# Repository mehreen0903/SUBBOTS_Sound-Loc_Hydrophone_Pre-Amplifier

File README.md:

# SUBBOTS_Sound-Loc_Hydrophone_Pre-Amplifier
This repo contains the PCB that acts as the pre-amplifier for the signal from the 5 hydrophones. This will later feed into the DE10.

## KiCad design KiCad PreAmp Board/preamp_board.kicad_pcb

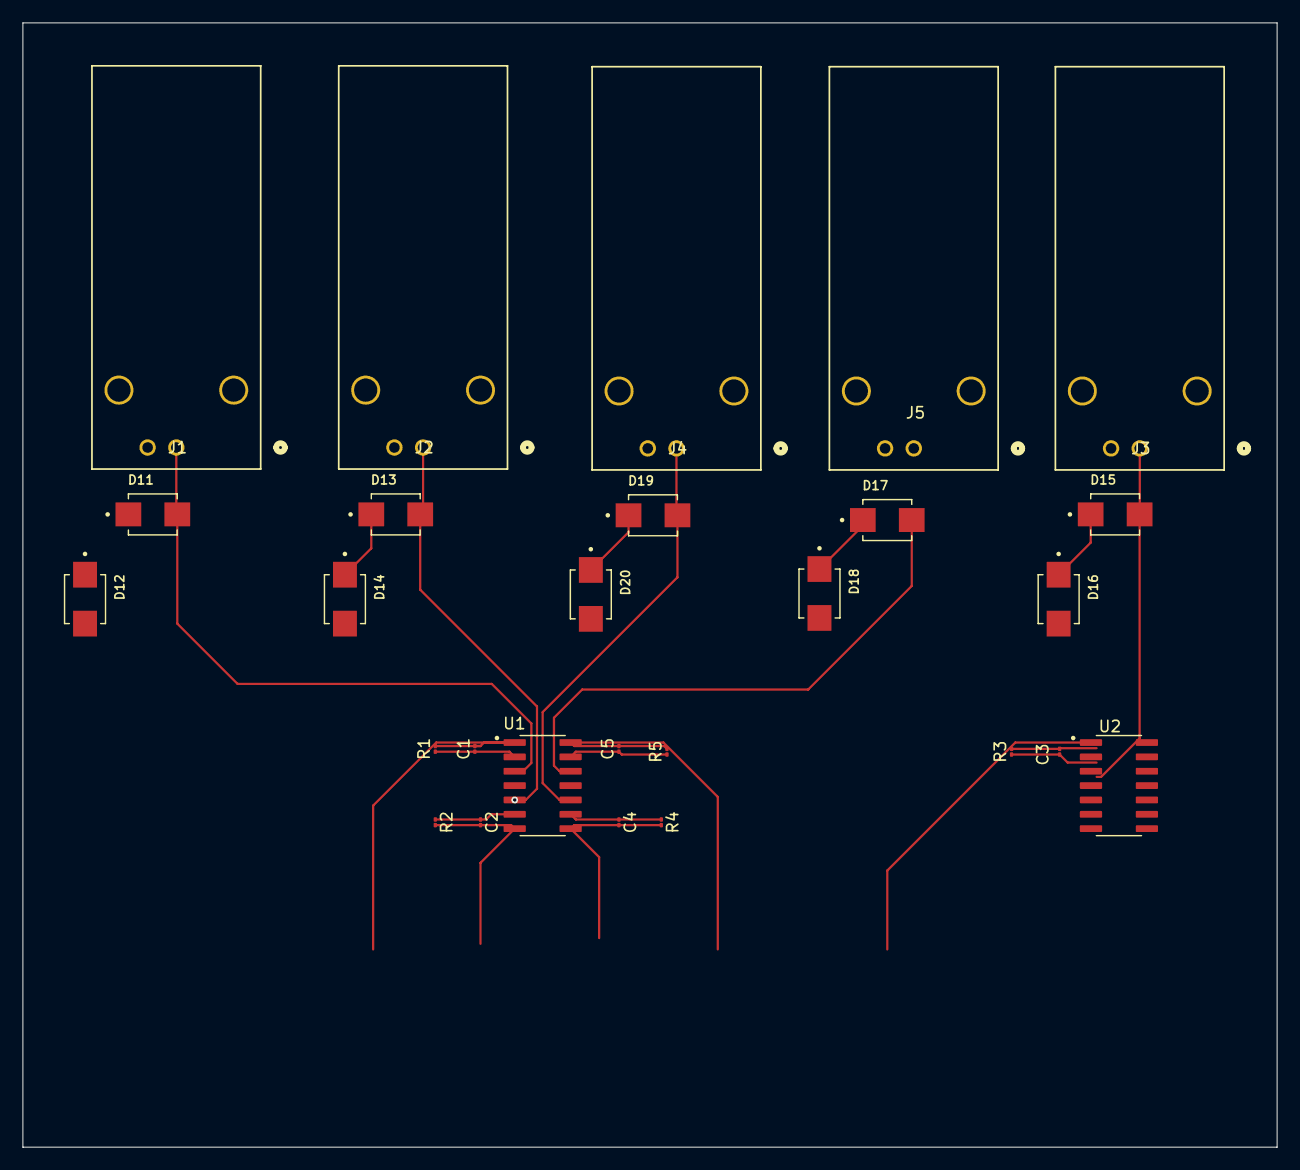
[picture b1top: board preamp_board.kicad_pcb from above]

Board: 2 copper layers, 111.0 x 99.5 mm, 27 parts (0 on the bottom side), 23 nets.

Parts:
C1, C2, C3, C4, C5: 1pF; C_01005_0402Metric
D11, D12, D13, D14, D15, D16, D17, D18, D19, D20: 1SMB5931H; DIOM4336X265N
J1, J2, J3, J4, J5: 731385033; CONN_73138-5033_MOL
R1, R2, R3, R4, R5: R; R_01005_0402Metric
U1, U2: LM324; SOIC127P600X175-14N

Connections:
+5V: U1.4, U2.4
-5V: U1.11, U2.11
GND: D12.A, D14.A, D16.A, D18.A, D20.A, J1.2, J2.2, J3.2, J4.2, J5.2
unnamed: C1.1, R1.1, U1.2
unnamed: C1.2, R1.2, U1.1
unnamed: C2.1, R2.1, U1.6
unnamed: C2.2, R2.2, U1.7
unnamed: C3.1, R3.1, U2.2
unnamed: C3.2, R3.2, U2.1
unnamed: C4.1, R4.1, U1.9
unnamed: C4.2, R4.2, U1.8
unnamed: C5.1, R5.1, U1.13
unnamed: C5.2, R5.2, U1.14
unnamed: D11.A, J1.1, U1.3
unnamed: D11.C, D12.C
unnamed: D13.A, J2.1, U1.5
unnamed: D13.C, D14.C
unnamed: D15.A, J3.1, U2.3
unnamed: D15.C, D16.C
unnamed: D17.A, J5.1, U1.12
unnamed: D17.C, D18.C
unnamed: D19.A, J4.1, U1.10
unnamed: D19.C, D20.C
